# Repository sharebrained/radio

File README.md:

radio
=====

Radio hardware and software projects, by Jared Boone of ShareBrained Technology, Inc.
You'll find software-defined radio designs and breakout boards for interesting components
(bandpass filters, VCO+PLL ICs, mixer ICs, LNAs).

Status
======

I intend to commit only projects that have been fabricated and tested to some extent in
the real world. But do check the README for each project to see more details.

Projects
========

* baseband_digitizer/
 * adc-iq-2185-xp2/: An 80MHz+ quadrature sampler using an FPGA and high-speed USB.
_
* front_end/
 * adrf6850-breakout/: Breakout board for the ADRF6850 100MHz to 1GHz receiver IC.

* vco_pll/
 * adf4350-breakout/: Breakout board for the ADF4350 VCO+PLL, tuning from 137.5MHz
   up to 4.4GHz.

License
=======

Designs are licensed under a
[Creative Commons Attribution-ShareAlike 3.0 Unported License]
(http://creativecommons.org/licenses/by-sa/3.0/) unless specified otherwise in the
project's README file.

Contact
=======

ShareBrained Technology, Inc.

<http://www.sharebrained.com/>

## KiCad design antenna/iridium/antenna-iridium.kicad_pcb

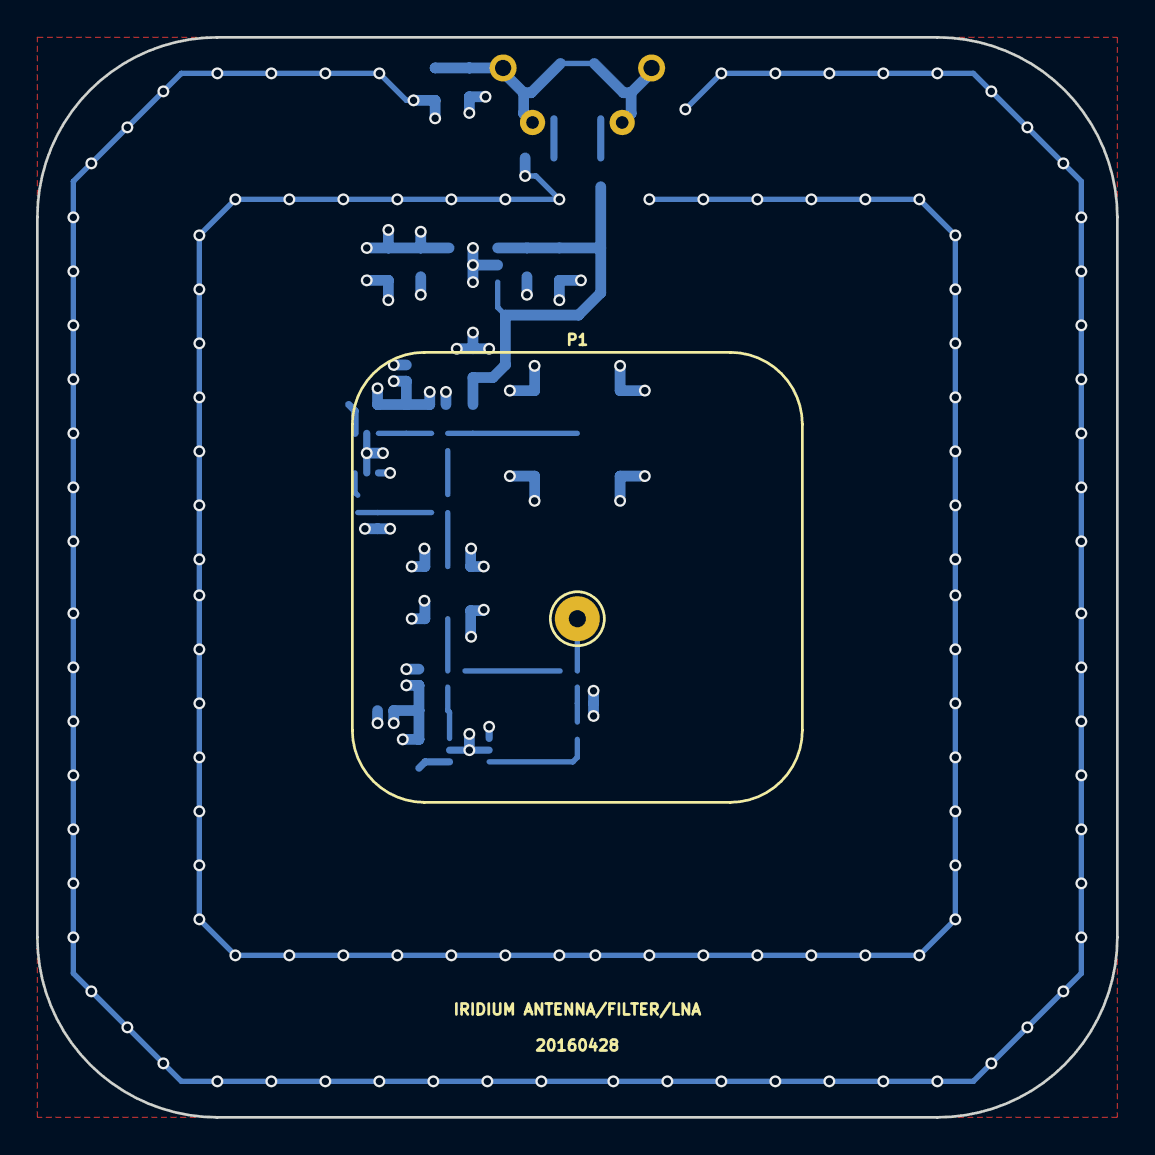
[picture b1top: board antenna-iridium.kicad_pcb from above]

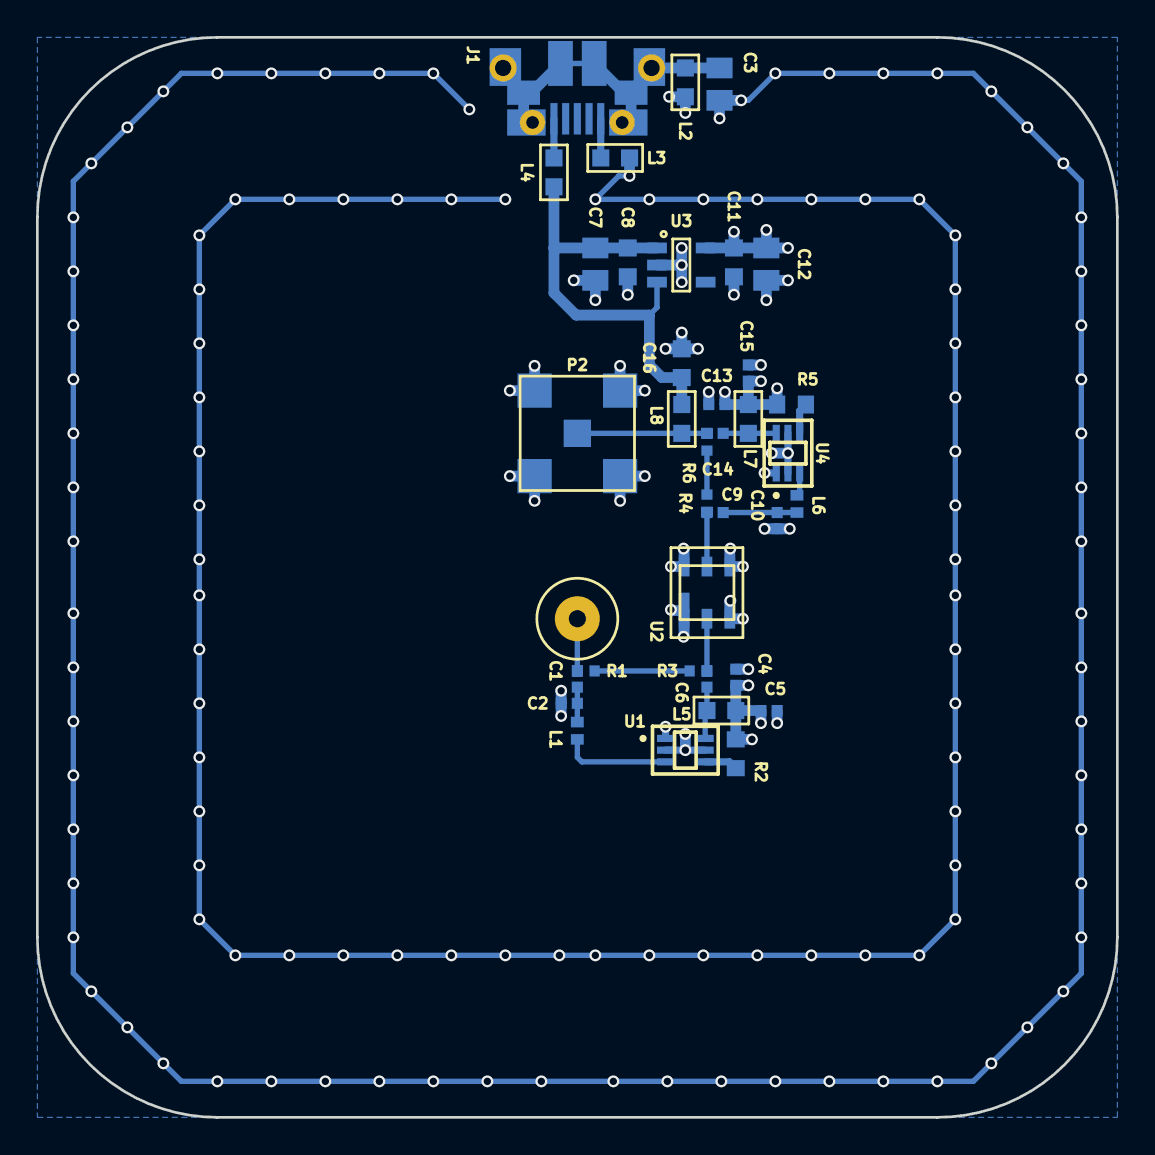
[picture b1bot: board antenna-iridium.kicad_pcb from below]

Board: 4 copper layers, 60.0 x 60.0 mm, 37 parts (36 on the bottom side), 20 nets.

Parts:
C1, C6, C9, C14: 22P; IPC_CAPC1005X55N
C2, C10: C; IPC_CAPC1005X55N
C3: 100N; IPC_CAPC2012X140N
C4, C13: 68P; IPC_CAPC1005X55N
C5, C15: 10N; IPC_CAPC1005X55N
C7, C12: 10U; IPC_CAPC2012X140N
C8, C11, C16: 100N; IPC_CAPC1608X95N
J1: GSG-USB-MICRO-B-SHIELDED; GSG-USB-MICROB-FCI-10103592
L1, L6: L; IPC_INDC1005X60N
L2, L3, L4, L8: L; IPC_INDC1608X95N
L5, L7: 47N; IPC_INDC1608X95N
P1: ANT; TAOGLAS_IP.1621.25.4.A.02
P2: CONN_COAX; MOLEX_0732511350
R1, R3, R4, R6: 0R; IPC_RESC1005X40N
R2, R5: 620R; IPC_RESC1608X55N
U1, U4: MGA-61563; IPC_SOT65P210X110-6N
U2: EPCOS_DCC6C
U3: ADP151_TSOT; IPC_SOT95P280X110-5N

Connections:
/V_RAW: C7.1, C8.1, C16.1, L4.1, L8.2, U3.1, U3.3
/V_REG: C4.1, C5.1, C11.1, C12.1, C13.1, C15.1, L5.2, L7.2, R2.1, R5.1, U3.5
GND: C2.2, C3.2, C4.2, C5.2, C7.2, C8.2, C10.2, C11.2, C12.2, C13.2, C15.2, C16.2, L2.1, L3.1, P2.2, U1.1, U1.2, U1.5, U2.1, U2.3, U2.4, U2.6, U3.2, U4.1, U4.2, U4.5
unnamed: C1.1, P1.1, R1.2
unnamed: C1.2, C2.1, L1.2
unnamed: C3.1, J1.0, L2.2
unnamed: C6.1, L5.1, U1.6
unnamed: C6.2, R3.1, U2.2
unnamed: C9.1, R4.1, U2.5
unnamed: C9.2, C10.1, L6.2
unnamed: C14.1, L7.1, U4.6
unnamed: C14.2, L8.1, P2.1, R6.1
unnamed: J1.1, L4.2
unnamed: J1.5, L3.2
unnamed: L1.1, U1.3
unnamed: L6.1, U4.3
unnamed: R1.1, R3.2
unnamed: R2.2, U1.4
unnamed: R4.2, R6.2
unnamed: R5.2, U4.4

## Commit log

2011-10-16 saw-dcc6e breakout board as sent to Laen's PCB order -- almost. I did tweak the schematic (switch to metric frame, add license info), and add identifying silkscreen to PCB.
2011-10-16 README list formatting fix.
2011-10-16 C'mon Markdown, work with me, work with me!
2011-10-16 Bill of materials clarification.
2011-10-16 Added URLs for EPCOS components. Changed URL to link for ShareBrained Web site.
2011-10-16 Cleaned up links and SAW component descriptions.
2011-10-16 Improved ShareBrained Web link.
2011-10-16 ShareBrained Web link formatting fix-up, part 2.
2011-10-16 Added information about files in repository, including link to Laen's PCB Order.
2011-10-16 Adjust formatting of files list.
2011-10-16 More files list formatting adjustment. Understanding Markdown via git commits is pretty tedious. There must be a better way...
2011-10-16 A couple of link-related formatting tweaks.
2011-10-16 Initial release of bpf-0805-4pc, a circuit board for 0805 SAW filters from TDK or Johanson/JTI.
2011-10-16 Initial commit of a balun breakout board for the Mini-Circuits TC1-1-13 transformer.
2011-10-19 Initial release of SAW-DCC6C breakout board, for EPCOS DCC6C SAW filters.
2011-10-25 Initial release of the ADF4350 breakout board, a wideband PLL+VCO tuning between 137.5 and 4,400 MHz.
2011-10-25 Corrected a bunch of filenames scrambled due to haphazard find-and-replace.
2011-10-25 Initial release of the Analog Devices ADRF6850 breakout board, a 100 MHz to 1 GHz receiver front-end with integrated VCO and PLL and quadrature baseband output.
2011-12-01 Release 20111106 of the ADC-IQ-2185-XP2 to Laen's PCB order.
2011-12-01 Add notes and adjust a few component values: XC6222 regulators require larger CL capacitor, especially for 1V2 device.
2012-03-07 Added phase noise measurement made 2011/12/20.
2012-03-07 Top cream stencil useful for mailing label laser cutting.
2012-03-07 Basic ADF4350 configuration and tuning via the pyBusPirateLite library for Bus Pirate 3.5 via SPI interface.
2012-05-04 Moved ADC-IQ-2185-XP2 baseband digitizer hardware into a new directory, to contain all related files (including non-hardware stuff).
2012-05-04 Changed ADRF6850 configuration to use external Vocm, for interfacing with my baseband digitizer board.
2012-05-04 Moved ADRF6850 project to front_end/ with hardware/ and software/ subdirectories.
2012-05-31 Moved adf4350-breakout files to radio/vco_pll/adf4350-breakout/ subdirectories.
2012-05-31 .gitignore to block EAGLE CAD .sch and .brd revision files.
2012-05-31 Updated README.md to reflect projects currently in repo.
2012-05-31 Oops, project relative URLs weren't right.
2012-05-31 OK, screw using repo URLs. I'll figure that out later.
2012-05-31 Moved adrf6850-breakout README from hardware/ to project root directory.
2012-05-31 Modified ADF4350-breakout license to specify BSD two-clause for the software portion.
2012-06-01 Added adc-iq-2185-xp2 BOM, schematic PDF, and README with license.
2014-08-13 SAW DCC6C filter PCB, initial design
    TODO: Ground plane cut-out under SMA pins to keep launch area at 50 Ohms.
2016-04-21 Iridium antenna initial commit
2016-04-29 Complete schematic, PCB routing in progress.
2016-04-29 Iridium antenna/filter/LNA routing complete.
2016-04-29 Silk clean-up/info, copper flood consistency.
2016-04-29 Very minor fixes.
2016-04-29 Added *-bak to the gitignore list.
2016-04-29 Review, remove filled_polygon data.
2016-04-29 Iridium antenna: Clean up schematic, add component values, update netlist.
2016-05-05 Iridium antenna: clean up design rules.
2016-05-05 Iridium antenna: Silk/mask clean-up, company name, make Gerbers.
2016-05-24 Update BOM, schematic with components ordered for first build.
